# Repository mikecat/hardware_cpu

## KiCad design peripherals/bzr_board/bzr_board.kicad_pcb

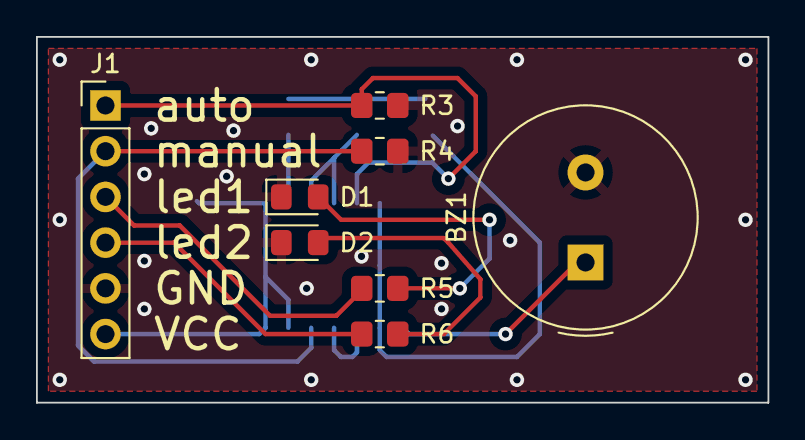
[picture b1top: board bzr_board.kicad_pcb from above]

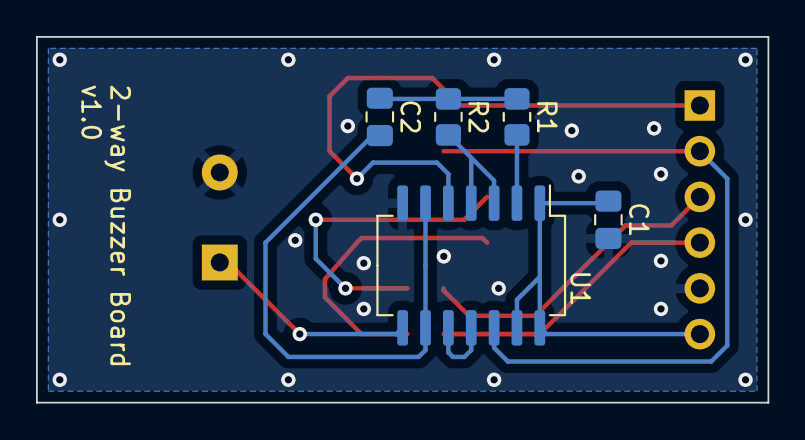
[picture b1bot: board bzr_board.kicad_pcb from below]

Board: 2 copper layers, 40.6 x 20.3 mm, 13 parts (5 on the bottom side), 14 nets.

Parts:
BZ1: Buzzer; Buzzer_TDK_PS1240P02BT_D12.2mm_H6.5mm
C1, C2: 0.1u; C_0805_2012Metric_Pad1.18x1.45mm_HandSolder
D1, D2: OSR50805C1C; LED_0805_2012Metric_Pad1.15x1.40mm_HandSolder
J1: Conn_01x06; PinHeader_1x06_P2.54mm_Vertical
R1, R2, R3, R4: 10k; R_0805_2012Metric_Pad1.20x1.40mm_HandSolder
R5, R6: 5k; R_0805_2012Metric_Pad1.20x1.40mm_HandSolder
U1: 74HC00; SO-14_5.3x10.2mm_P1.27mm

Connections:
/auto: J1.1, R3.1, U1.5
/led1: J1.3, R5.1
/led2: J1.4, R6.1
/manual: J1.2, R4.1, U1.12
GND: BZ1.2 (+), C1.2, D1.1 (K), D2.1 (K), J1.5, R3.2, R4.2, U1.7 (GND)
unnamed: BZ1.1 (-), U1.8
unnamed: C2.1, R1.1, R2.1
unnamed: C2.2, U1.6, U1.9
unnamed: D1.2 (A), R5.2
unnamed: D2.2 (A), R6.2
unnamed: R1.2, U1.2
unnamed: R2.2, U1.3, U1.4
unnamed: U1.10, U1.11
VCC: C1.1, J1.6, U1.1, U1.13, U1.14 (VCC)

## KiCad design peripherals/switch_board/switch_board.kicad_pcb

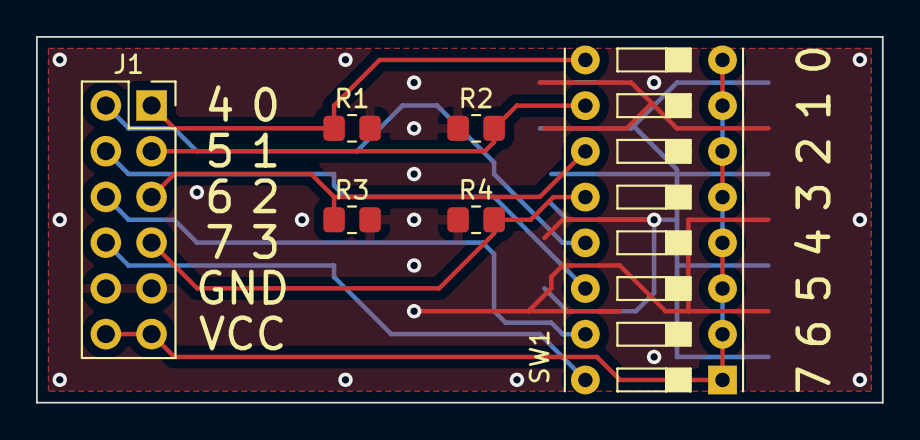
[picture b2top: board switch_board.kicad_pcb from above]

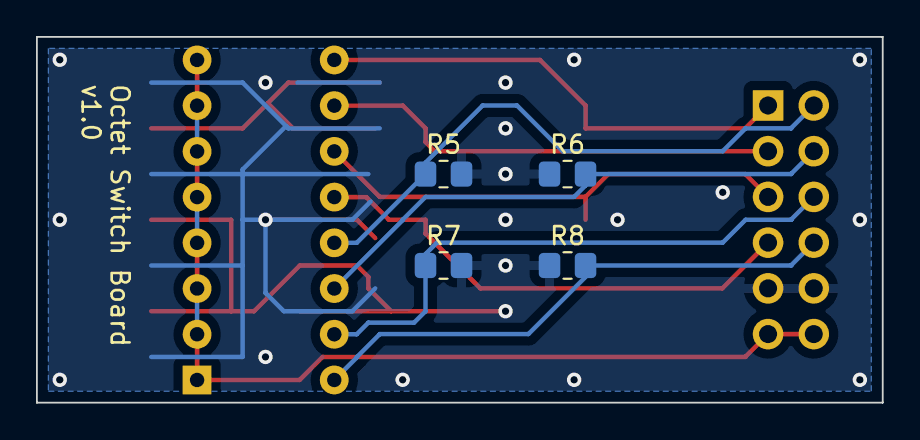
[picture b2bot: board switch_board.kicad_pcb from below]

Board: 2 copper layers, 47.0 x 20.3 mm, 10 parts (4 on the bottom side), 10 nets.

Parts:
J1: Conn_02x06_Top_Bottom; PinSocket_2x06_P2.54mm_Vertical_Top_Bottom
R1, R2, R3, R4, R5, R6, R7, R8: 10k; R_0805_2012Metric_Pad1.20x1.40mm_HandSolder
SW1: SW_DIP_x08; SW_DIP_SPSTx08_Slide_9.78x22.5mm_W7.62mm_P2.54mm_short

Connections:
/s0: J1.1, R1.1, SW1.9
/s1: J1.2, R2.1, SW1.10
/s2: J1.3, R3.1, SW1.11
/s3: J1.4, R4.1, SW1.12
/s4: J1.7, R5.1, SW1.13
/s5: J1.8, R6.1, SW1.14
/s6: J1.9, R7.1, SW1.15
/s7: J1.10, R8.1, SW1.16
GND: J1.5, J1.11, R1.2, R2.2, R3.2, R4.2, R5.2, R6.2, R7.2, R8.2
VCC: J1.6, J1.12, SW1.1, SW1.2, SW1.3, SW1.4, SW1.5, SW1.6, SW1.7, SW1.8
